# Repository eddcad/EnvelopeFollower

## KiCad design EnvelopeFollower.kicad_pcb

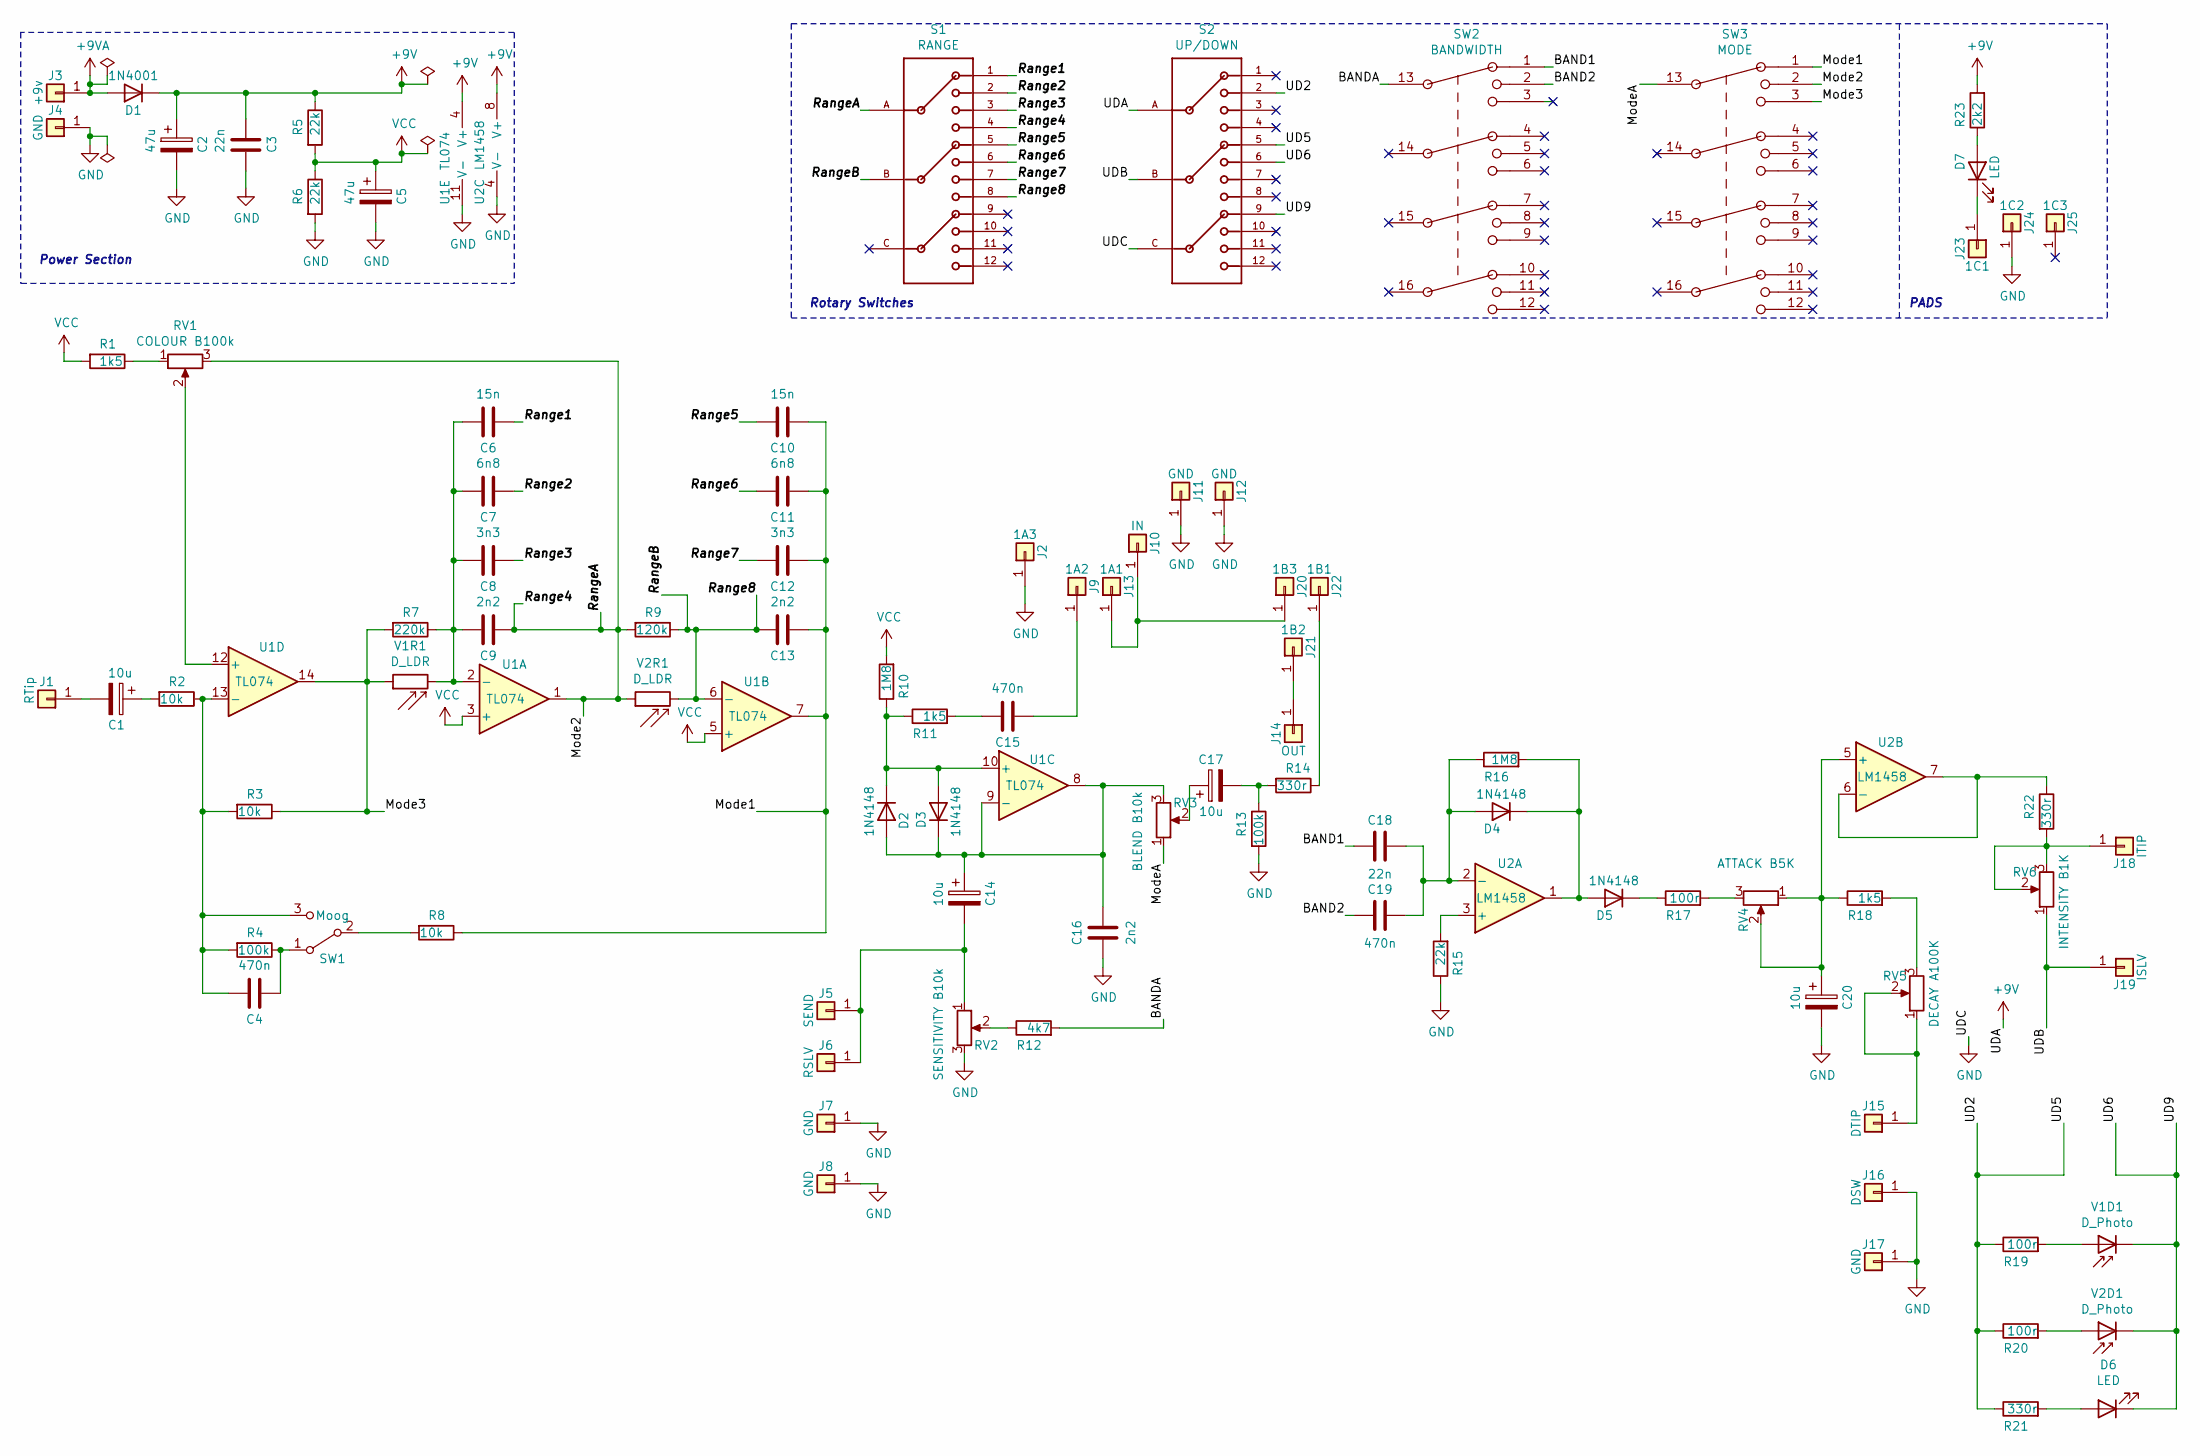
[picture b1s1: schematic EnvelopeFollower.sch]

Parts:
C1, C14, C17, C20: 10u; CP_Radial_D5.0mm_P2.00mm
C2: 47u; CP_Radial_D5.0mm_PWideForPower
C3, C18: 22n; C_Rect_L7.0mm_W2.5mm_P5.00mm
C4, C15, C19: 470n; C_Rect_L7.0mm_W3.5mm_P5.00mm
C5: 47u; CP_Radial_D5.0mm_P2.00mm
C6, C10: 15n; C_Rect_L7.0mm_W2.5mm_P5.00mm
C7, C11: 6n8; C_Rect_L7.0mm_W2.5mm_P5.00mm
C8, C12: 3n3; C_Rect_L7.0mm_W2.5mm_P5.00mm
C9, C13, C16: 2n2; C_Rect_L7.0mm_W2.5mm_P5.00mm
D1: 1N4001; D_DO-41_SOD81_P10.16mm_Horizontal
D2, D3, D4, D5: 1N4148; D_DO-35_SOD27_P7.62mm_Horizontal
D6, D7: LED; LED_D5.0mm
J1: RTip; SolderWire-0.25sqmm_1x01_D0.65mm_OD1.7mm
J2: 1A3; SolderWire-0.25sqmm_1x01_D0.65mm_OD1.7mm
J3: +9v; SolderWire-0.25sqmm_1x01_D0.65mm_OD1.7mm
J4, J7, J8, J11, J12, J17: GND; SolderWire-0.25sqmm_1x01_D0.65mm_OD1.7mm
J5: SEND; SolderWire-0.25sqmm_1x01_D0.65mm_OD1.7mm
J6: RSLV; SolderWire-0.25sqmm_1x01_D0.65mm_OD1.7mm
J9: 1A2; SolderWire-0.25sqmm_1x01_D0.65mm_OD1.7mm
J10: IN; SolderWire-0.25sqmm_1x01_D0.65mm_OD1.7mm
J13: 1A1; SolderWire-0.25sqmm_1x01_D0.65mm_OD1.7mm
J14: OUT; SolderWire-0.25sqmm_1x01_D0.65mm_OD1.7mm
J15: DTIP; SolderWire-0.25sqmm_1x01_D0.65mm_OD1.7mm
J16: DSW; SolderWire-0.25sqmm_1x01_D0.65mm_OD1.7mm
J18: ITIP; SolderWire-0.25sqmm_1x01_D0.65mm_OD1.7mm
J19: ISLV; SolderWire-0.25sqmm_1x01_D0.65mm_OD1.7mm
J20: 1B3; SolderWire-0.25sqmm_1x01_D0.65mm_OD1.7mm
J21: 1B2; SolderWire-0.25sqmm_1x01_D0.65mm_OD1.7mm
J22: 1B1; SolderWire-0.25sqmm_1x01_D0.65mm_OD1.7mm
J23: 1C1; SolderWire-0.25sqmm_1x01_D0.65mm_OD1.7mm
J24: 1C2; SolderWire-0.25sqmm_1x01_D0.65mm_OD1.7mm
J25: 1C3; SolderWire-0.25sqmm_1x01_D0.65mm_OD1.7mm
R1, R11, R18: 1k5; R_Axial_DIN0207_L6.3mm_D2.5mm_P7.62mm_Horizontal
R2, R3, R8: 10k; R_Axial_DIN0207_L6.3mm_D2.5mm_P7.62mm_Horizontal
R4, R13: 100k; R_Axial_DIN0207_L6.3mm_D2.5mm_P7.62mm_Horizontal
R5, R6, R15: 22k; R_Axial_DIN0207_L6.3mm_D2.5mm_P7.62mm_Horizontal
R7: 220k; R_Axial_DIN0207_L6.3mm_D2.5mm_P7.62mm_Horizontal
R9: 120k; R_Axial_DIN0207_L6.3mm_D2.5mm_P7.62mm_Horizontal
R10, R16: 1M8; R_Axial_DIN0207_L6.3mm_D2.5mm_P7.62mm_Horizontal
R12: 4k7; R_Axial_DIN0207_L6.3mm_D2.5mm_P7.62mm_Horizontal
R14, R21, R22: 330r; R_Axial_DIN0207_L6.3mm_D2.5mm_P7.62mm_Horizontal
R17, R19, R20: 100r; R_Axial_DIN0207_L6.3mm_D2.5mm_P7.62mm_Horizontal
R23: 2k2; R_Axial_DIN0207_L6.3mm_D2.5mm_P7.62mm_Horizontal
RV1: COLOUR B100k; Potentiometer_Omeg_PC16BU_Vertical
RV2: SENSITIVITY B10k; Potentiometer_Omeg_PC16BU_Vertical
RV3: BLEND B10k; Potentiometer_Omeg_PC16BU_Vertical
RV4: ATTACK B5K; Potentiometer_Omeg_PC16BU_Vertical
RV5: DECAY A100K; Potentiometer_Omeg_PC16BU_Vertical
RV6: INTENSITY B1K; Potentiometer_Omeg_PC16BU_Vertical
S1: RANGE; 3p4tRotary
S2: UP/DOWN; 3p4tRotary
SW1: Moog; SWITCH_SPDT_PTH_12.9X6.9MM
SW2: BANDWIDTH; LORINCK1049
SW3: MODE; LORINCK1049
U1: TL074; DIP-14_W7.62mm
U2: LM1458; DIP-8_W7.62mm
V1D1, V2D1: D_Photo; LED_D5.0mm
V1R1, V2R1: D_LDR; R_LDR_5.2x5.2mm_P3.5mm_Horizontal

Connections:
+9V: C2.1, C3.1, D1.1 (K), R5.1, R23.2, S2.A, U1.4 (V+), U2.8 (V+)
+9VA: D1.2 (A), J3.1
/BAND1: C18.1, SW2.1
/BAND2: C19.1, SW2.2
/BANDA: R12.2, SW2.13 (A)
/Mode1: C10.1, C11.1, C12.1, C13.1, R8.1, SW3.1, U1.7
/Mode2: C9.1, R9.2, RV1.3, S1.4, S1.A, SW3.2, U1.1, V2R1.1
/Mode3: R3.1, R7.2, SW3.3, U1.14, V1R1.1
/ModeA: RV3.1, SW3.13 (A)
/Range1: C6.1, S1.1
/Range2: C7.1, S1.2
/Range3: C8.1, S1.3
/Range5: C10.2, S1.5
/Range6: C11.2, S1.6
/Range7: C12.2, S1.7
/Range8: C13.2, R9.1, S1.8, S1.B, U1.6 (-), V2R1.2
/UD2: R19.1, R20.1, R21.1, S2.2, S2.5
/UD6: D6.1 (K), S2.6, S2.9, V1D1.1 (K), V2D1.1 (K)
/UDB: J19.1, RV6.1, S2.B
GND: C2.2, C3.2, C5.2, C16.1, C20.2, J2.1, J4.1, J7.1, J8.1, J11.1, J12.1, J16.1, J17.1, J24.1, R6.2, R13.2, R15.1, RV2.3, S2.C, U1.11 (V-), U2.4 (V-)
unnamed: C1.1, R2.2
unnamed: C1.2, J1.1
unnamed: C4.1, R4.1, SW1.1 (A)
unnamed: C4.2, R2.1, R3.2, R4.2, SW1.3 (C), U1.13 (-)
unnamed: C6.2, C7.2, C8.2, C9.2, R7.1, U1.2 (-), V1R1.2
unnamed: C14.1, C16.2, D2.2 (A), D3.1 (K), RV3.3, U1.8, U1.9 (-)
unnamed: C14.2, J5.1, J6.1, RV2.1
unnamed: C15.1, J9.1
unnamed: C15.2, R11.2
unnamed: C17.1, RV3.2
unnamed: C17.2, R13.1, R14.2
unnamed: C18.2, C19.2, D4.2 (A), R16.1, U2.2 (-)
unnamed: C20.1, R18.1, RV4.1, RV4.2, U2.5 (+)
unnamed: D2.1 (K), D3.2 (A), R10.1, R11.1, U1.10 (+)
unnamed: D4.1 (K), D5.2 (A), R16.2, U2.1
unnamed: D5.1 (K), R17.1
unnamed: D6.2 (A), R21.2
unnamed: D7.1 (K), J23.1
unnamed: D7.2 (A), R23.1
unnamed: J10.1, J13.1, J20.1
unnamed: J14.1, J21.1
unnamed: J15.1, RV5.1, RV5.2
unnamed: J18.1, R22.2, RV6.2, RV6.3
unnamed: J22.1, R14.1
unnamed: R1.1, RV1.1
unnamed: R8.2, SW1.2 (B)
unnamed: R12.1, RV2.2
unnamed: R15.2, U2.3 (+)
unnamed: R17.2, RV4.3
unnamed: R18.2, RV5.3
unnamed: R19.2, V1D1.2 (A)
unnamed: R20.2, V2D1.2 (A)
unnamed: R22.1, U2.6 (-), U2.7
unnamed: RV1.2, U1.12 (+)
VCC: C5.1, R1.2, R5.2, R6.1, R10.2, U1.3 (+), U1.5 (+)

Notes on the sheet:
Power Section
Rotary Switches
PADS

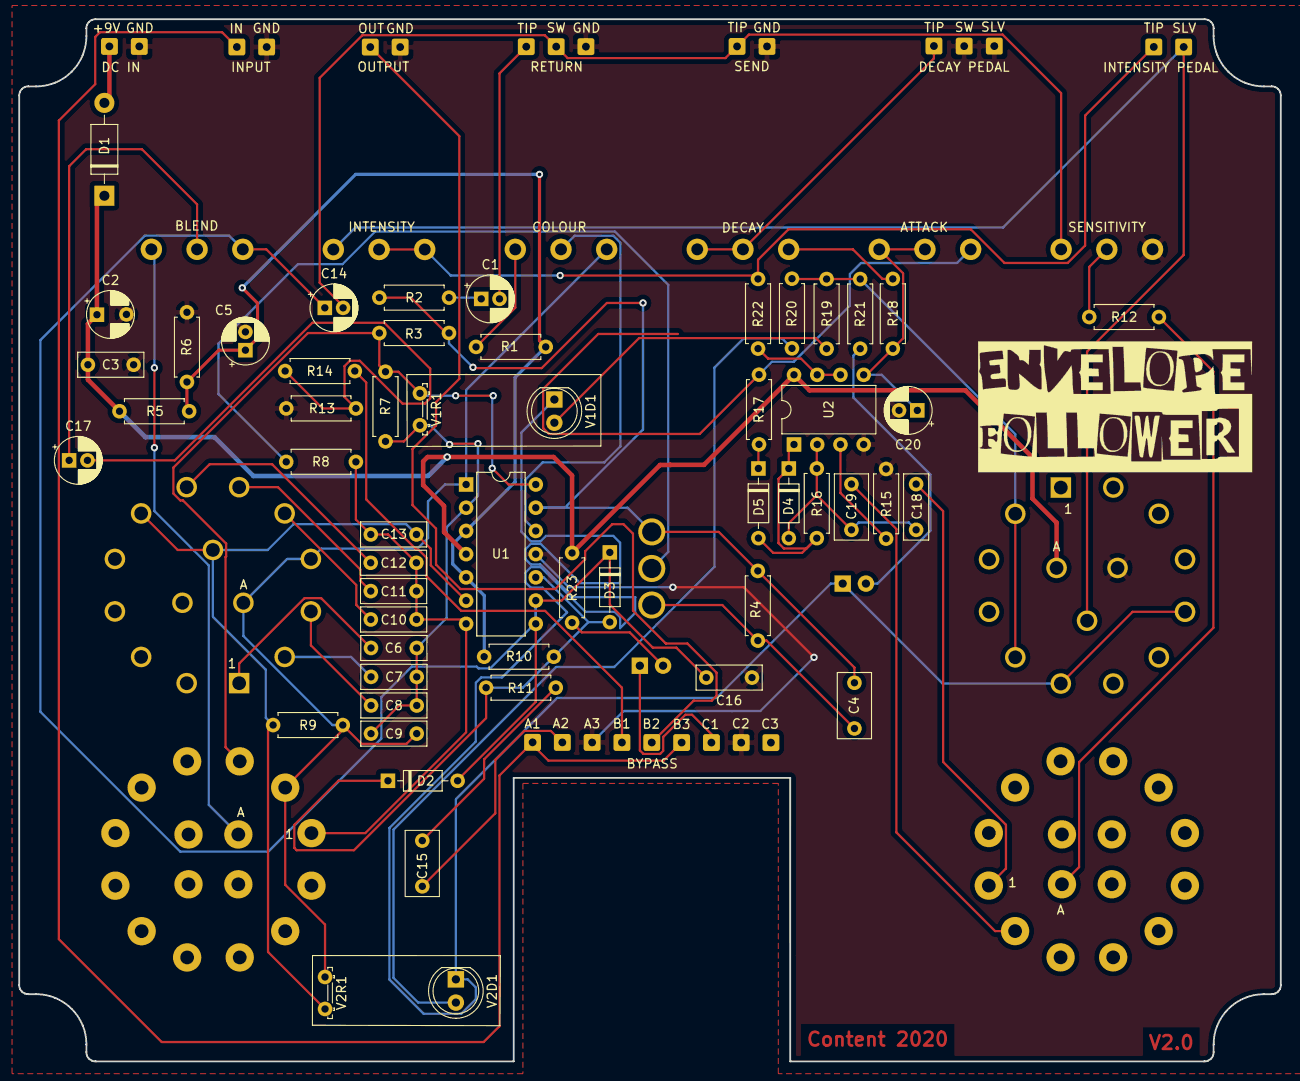
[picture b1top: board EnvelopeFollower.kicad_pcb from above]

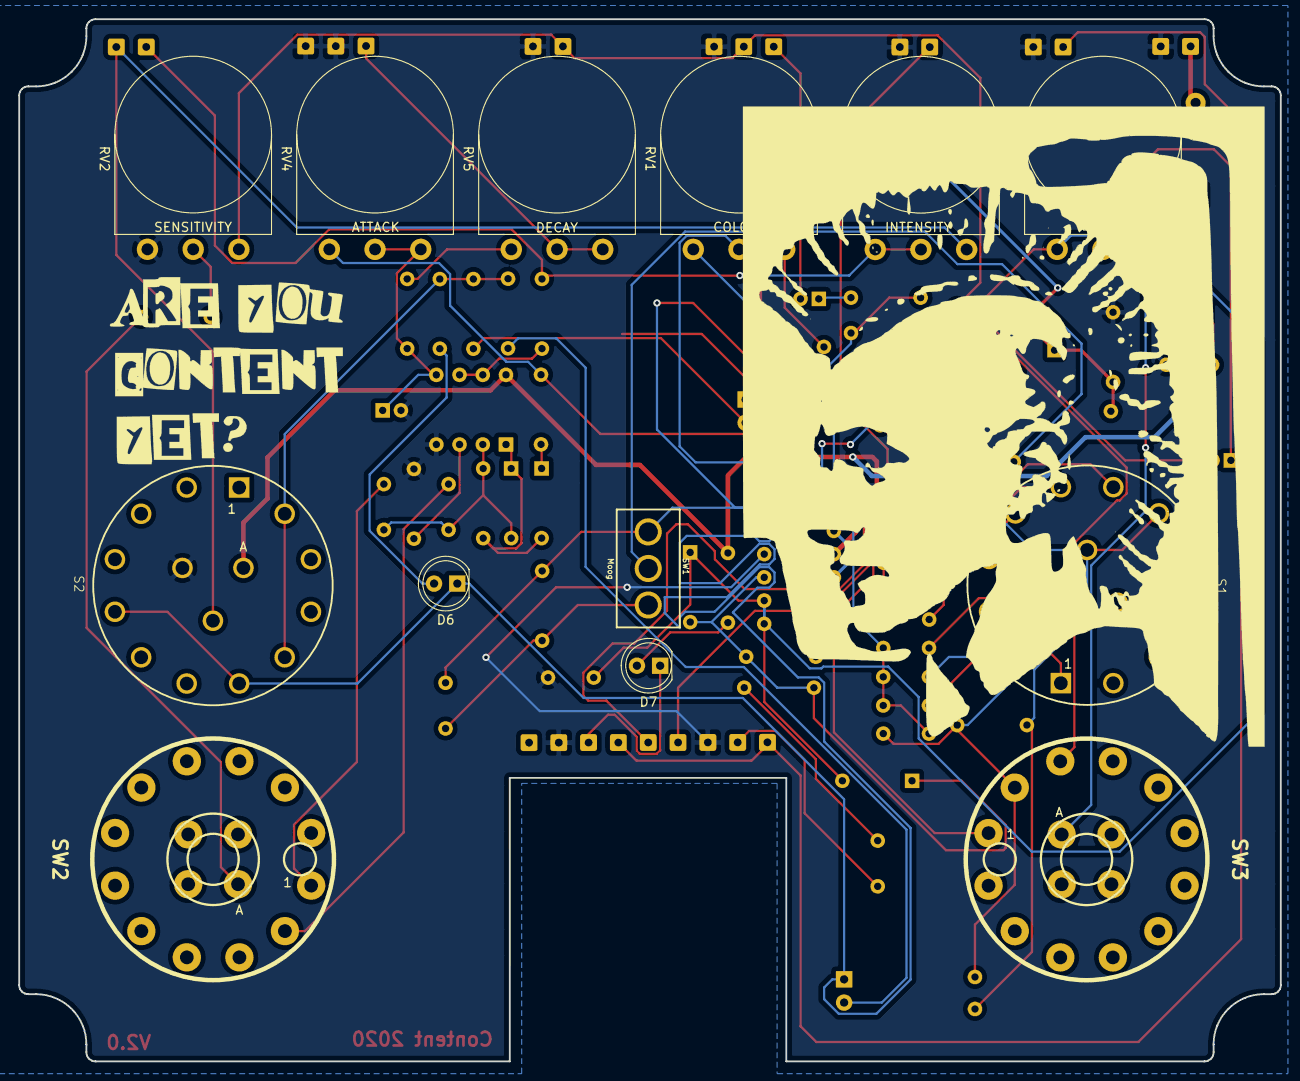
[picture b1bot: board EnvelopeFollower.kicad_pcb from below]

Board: 2 copper layers, 138.0 x 114.0 mm, 92 parts (13 on the bottom side), 55 nets.

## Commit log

2020-09-11 I forgot to add these
2020-09-20 V2.00 provisionaly completed
2020-10-09 cleaned up silks
2020-11-12 Added license
